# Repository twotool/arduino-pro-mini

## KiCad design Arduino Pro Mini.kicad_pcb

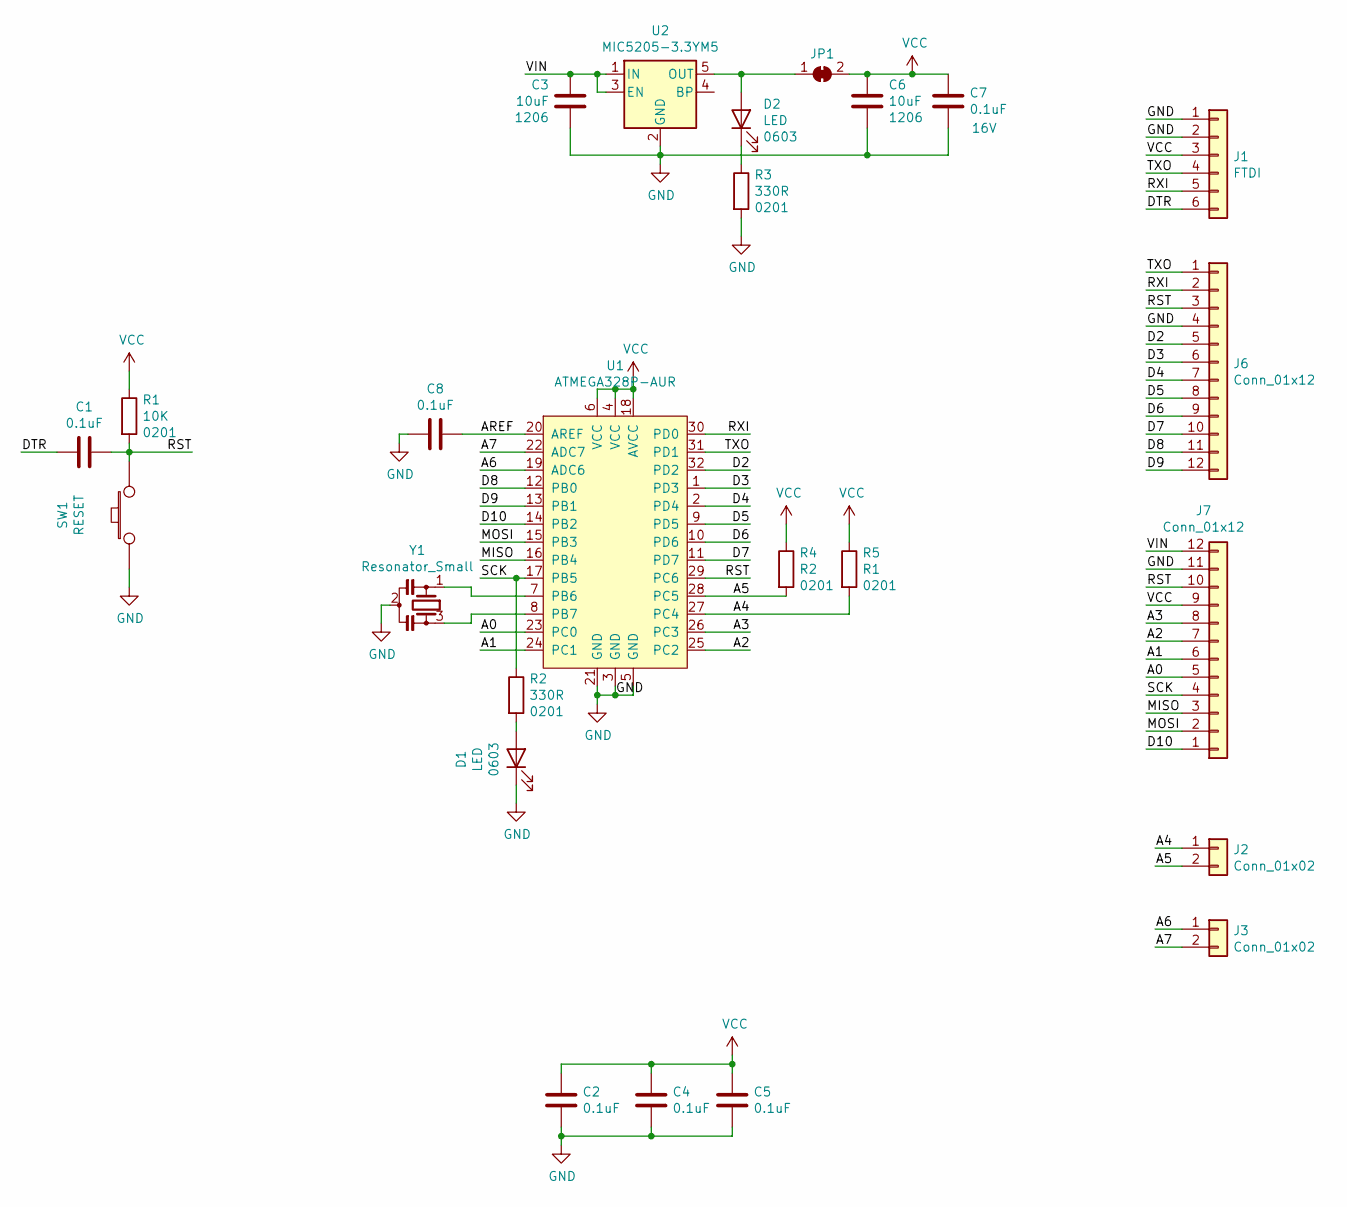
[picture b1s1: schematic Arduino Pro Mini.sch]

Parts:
C1, C2, C4, C5, C7, C8: 0.1uF; C_0201_0603Metric
C3, C6: 10uF; C_1206_3216Metric
D1, D2: LED; LED_0603_1608Metric
J1: FTDI; PinHeader_1x06_P2.54mm_Horizontal
J2, J3: Conn_01x02; PinHeader_1x02_P2.54mm_Vertical
J6, J7: Conn_01x12; PinHeader_1x12_P2.54mm_Vertical
JP1: SolderJumper_2_Bridged; SolderJumper-2_P1.3mm_Bridged_Pad1.0x1.5mm
R1: 10K; R_0201_0603Metric
R2, R3: 330R; R_0201_0603Metric
R4: R2; R_0201_0603Metric
R5: R1; R_0201_0603Metric
SW1: RESET; SW_SPST_CK_RS282G05A3
U1: ATMEGA328P-AUR; TQFP-32_7x7mm; MPN ATMEGA328P-AUR; Digi-Key_PN ATMEGA328P-AURCT-ND
U2: MIC5205-3.3YM5; SOT-23-5
Y1: Resonator_Small; Resonator_SMD_muRata_CSTxExxV-3Pin_3.0x1.1mm

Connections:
/A0: J7.5, U1.23 (PC0)
/A1: J7.6, U1.24 (PC1)
/A2: J7.7, U1.25 (PC2)
/A3: J7.8, U1.26 (PC3)
/A4: J2.1, R5.2, U1.27 (PC4)
/A5: J2.2, R4.2, U1.28 (PC5)
/A6: J3.1, U1.19 (ADC6)
/A7: J3.2, U1.22 (ADC7)
/AREF: C8.1, U1.20 (AREF)
/D2: J6.5, U1.32 (PD2)
/D3: J6.6, U1.1 (PD3)
/D4: J6.7, U1.2 (PD4)
/D5: J6.8, U1.9 (PD5)
/D6: J6.9, U1.10 (PD6)
/D7: J6.10, U1.11 (PD7)
/D8: J6.11, U1.12 (PB0)
/D9: J6.12, U1.13 (PB1)
/D10: J7.1, U1.14 (PB2)
/DTR: C1.2, J1.6
/MISO: J7.3, U1.16 (PB4)
/MOSI: J7.2, U1.15 (PB3)
/RST: C1.1, J6.3, J7.10, R1.2, SW1.2, U1.29 (PC6); also elsewhere on the board
/RXI: J1.5, J6.2, U1.30 (PD0)
/SCK: J7.4, R2.1, U1.17 (PB5)
/TXO: J1.4, J6.1, U1.31 (PD1)
/VIN: C3.1, J7.12, U2.1 (IN), U2.3 (EN)
GND: C2.2, C3.2, C4.2, C5.2, C6.2, C7.2, C8.2, D1.1 (K), J1.1, J1.2, J6.4, J7.11, R3.2, SW1.1, U1.3 (GND), U1.5 (GND), U1.21 (GND), U2.2 (GND), Y1.2; also elsewhere on the board
unnamed: D1.2 (A), R2.2
unnamed: D2.1 (K), R3.1
unnamed: D2.2 (A), JP1.1 (A), U2.5 (OUT)
unnamed: U1.7 (PB6), Y1.1
unnamed: U1.8 (PB7), Y1.3
VCC: C2.1, C4.1, C5.1, C6.1, C7.1, J1.3, J7.9, JP1.2 (B), R1.1, R4.1, R5.1, U1.4 (VCC), U1.6 (VCC), U1.18 (AVCC)

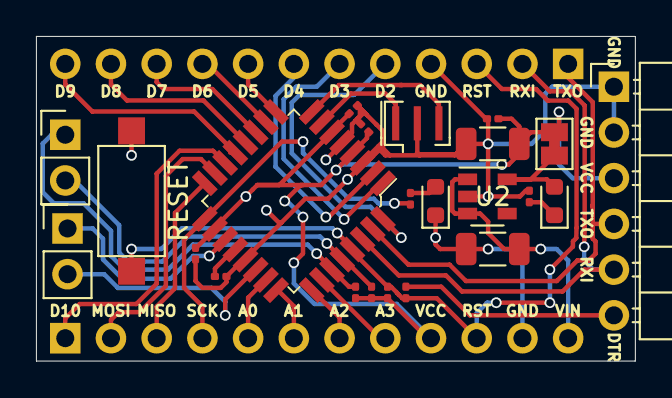
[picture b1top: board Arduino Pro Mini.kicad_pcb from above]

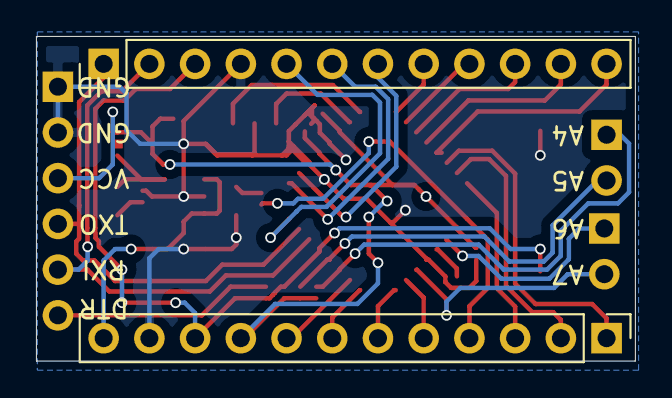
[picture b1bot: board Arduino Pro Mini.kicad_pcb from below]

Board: 2 copper layers, 33.3 x 18.0 mm, 25 parts (2 on the bottom side), 33 nets.

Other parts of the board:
RESET: RESET; SW_SPST_CK_RS282G05A3

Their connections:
/RST: RESET.2; also elsewhere on the board
GND: RESET.1; also elsewhere on the board

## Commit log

2022-07-24 Arduino Pro mini first commit
2022-07-24 added .gitignore
